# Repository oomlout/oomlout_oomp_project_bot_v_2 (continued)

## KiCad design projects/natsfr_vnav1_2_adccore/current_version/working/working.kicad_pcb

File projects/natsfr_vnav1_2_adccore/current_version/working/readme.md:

# vnav1_2
 
## summary 
* id: natsfr_vnav1_2_adccore
* user: natsfr
* name: vnav1_2
* board: adccore
* repo: https://github.com/natsfr/VNAV1.2
* src_file_repo_kicad_pcb: board/VNAV1/adccore.kicad_pcb
* src_file_repo_kicad_pcb_link: https://github.com/natsfr/VNAV1.2/tree/master/board/VNAV1/adccore.kicad_pcb
* src_file_repo_kicad_sch: board/VNAV1/ad4355.kicad_sch
* src_file_repo_kicad_sch_link: https://github.com/natsfr/VNAV1.2/tree/master/board/VNAV1/ad4355.kicad_sch

* src_file_repo_sch: 
* src_file_repo_sch_link: https://github.com/natsfr/VNAV1.2/tree/master/
* full details link: https://github.com/oomlout/oomlout_oomp_project_bot_v_2/tree/main/projects/natsfr_vnav1_2_adccore/current_version/working

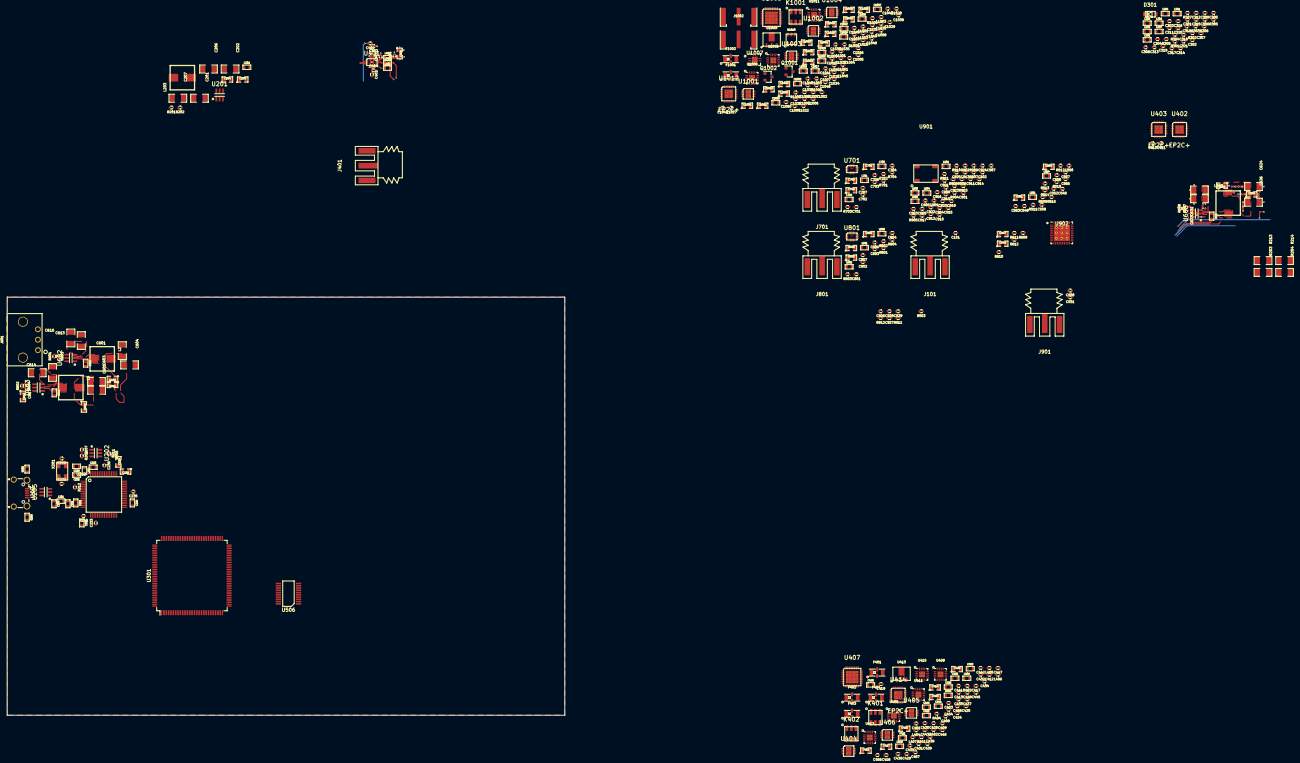
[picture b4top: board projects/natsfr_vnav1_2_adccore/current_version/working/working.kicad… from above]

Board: 4 copper layers, 160.0 x 120.0 mm, 419 parts (1 on the bottom side), 264 nets.

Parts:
C101, C401, C402, C403, C404, C406, C407, C410, C411, C701, C702, C703, C704, C706, C707, C801, C802, C803, C804, C806, C807: CAP_0402; SM0402
C201, C202, C206, C207, C601, C603, C604, C605, C613, C614, C616, C617, C624, C626, C631, C633: 10uF; SM1206
C204, C608, C609, C628: 100nF; SM0805
C205, C611, C612, C630, C1050, C1051, C1053, C1056: 1uF; SM0805
C208, C618, C619, C637: 100nF; SM0603
C221, C223, C224: 100n; SM0603
C222, C226: 10p; SM0402
C225, C229: 4.7u; SM0805
C227: 1uF; SM0603
C228, C230, C231, C232: CAP_0603; SM0603
C233, C234, C235, C236: 100n; SM0402
C301, C302, C304, C305, C307, C308, C310, C311, C313, C314, C316, C317, C319, C320, C548, C549, C550, C552, C555, C901, C902, C904, C906, C907, C908, C909, C911, C912, C914, C916, C919, C920, C923, C926, C927, C928, C929: 10nF; SM0402
C303, C306, C309, C312, C315, C318, C321, C433, C434, C441, C553, C556, C903, C905, C910, C913, C915, C917, C922, C924: 100pF; SM0402
C405, C705, C805: CAP_0805; SM0805
C408, C412, C424, C429, C430, C432, C438, C440, C557, C921, C925, C930, C931, C1001, C1003, C1015, C1021, C1022, C1028, C1032, C1034, C1041: 100nF; SM0402
C409, C413, C417, C425, C431, C437, C439, C443, C558, C1002, C1004, C1005, C1016, C1027, C1031, C1033, C1036, C1037, C1040, C1055, C1059, C1060, C1061: 10pF; SM0402
C414, C415, C416, C426, C427, C428, C1008, C1009, C1010, C1011, C1023, C1024, C1025, C1026: 10uF; SM0805
C418, C1006: 390pF; SM0402
C419, C1007: 33nF; SM0402
C420, C1012: 1500pF; SM0402
C421, C422, C423, C1017, C1018, C1019, C1020: 1nF; SM0603
C435, C436, C442, C454, C456, C457, C458, C1029, C1030, C1035, C1049, C1054: 22pF; SM0402
C444, C446, C448, C450, C452, C455, C1038, C1047, C1052, C1057: 47nF; SM0603
C445, C447, C449, C451, C453, C1039, C1048, C1058: 22p; SM0402
C551, C554: 4.7uF; SM0805
C646, C647, C708, C709, C808, C809: 100uF; SM0805
C918: 15pF; SM0402
C1042, C1043, C1046: 1nF; SM0402
C1044: 5.6pF; SM0402
C1045: 18pF; SM0402
D301: DIODE; SOD-123
F401: LFCN-2500+; FV1206
F402, F1001: LFCN-7200+; FV1206
F403: LFCN-1400+; FV1206
F404, F1002: LFCN-5000+; FV1206
J101, J901: LO Ref output; SMA_AMP_132255-12
J202: USB_OTG; USB_Micro-B_Wuerth_629105150521_CircularHoles
J401, J701, J801: SMA_PCB; SMA_AMP_132255-12
J601: Conn_01x03; MICROFIT_3POS_FEM_43650-0303
J1001: DUT_OUT_1; CINCH_142-0701-881
J1002: DUT_OUT_2; CINCH_142-0701-881
K401, K402, K1001: TCM1-83X-1+; DB1627
L2, L3, L203, L603: 2.2uH; IND_7x7x4.5
L201, L202, L401, L402, L403, L701, L702, L703, L801, L802, L803: IND_0603; SM0603
L301, L302, L303, L304, L305, L306, L307, L501, L514, L901, L902, L903, L904: BLM18; SM0603
L404, L405, L406, L407, L1001, L1002: 7.5nH; SM0402
L408, L1006: 33n; SM0603
L1003: NC; SM0402
L1004, L1005: IND_0805; SM0805
Q1001: BSS84; SOT-23
Q1002: BSS138; SOT-23
R201, R207, R208, R211, R306, R307, R601, R602, R607, R1007, R1008, R1009: 10k; SM0402
R202: 65k; SM0402
R203, R204, R213, R214: RES_1206; SM1206
R205, R206: NP; SM0603
R209: 2.2k; SM0402
R210, R403, R509, R510, R511, R512, R513, R514, R903, R904, R905, R906, R1004: 1k; SM0402
R212: 12k; SM0402
R301, R302, R303, R304, R305, R308, R515, R612, R704, R804: 0; SM0402
R401, R404, R1001, R1002, R1005: 4.7k; SM0402
R402, R901, R902, R1003: RES_0402; SM0402
R405: 49; SM0603
R503, R907, R908, R909, R910: 50; SM0402
R603: 31.6k; SM0402
R604: 4.99k; SM0402
R608: 52.3k; SM0402
R609, R610, R701, R702, R801, R802: 25; SM0402
R611, R703, R803: DNI; SM0402
R911, R912: 100; SM0402
R1006: 38; SM0603
U201, U602, U603, U606: TPS563208_SOT236; SOT-236-095mm
U202: 93LC46B; SOT-236-095mm
U203: FT2232H; LQFP_64
U205: TPD4E1U06-SC70; SOT-236-095mm
U301: ICE40HX1K-TQ144; TQFP-144_20x20mm_P0.5mm
U401, U701, U801: LTC5548; QFN12_2x3mm_UDB_LT
U402, U403, U414, U1012: EP2C+; QFN24_4x4_0.5mm
U404, U1001, U1002: ADM7170ACPZ-5.0; DFN8_3x3mm
U405, U406, U1003, U1004: ADM7170ACPZ-3.3; DFN8_3x3mm
U407: ADF4355; QFN32_5x5mm_3.6mm
U408, U409, U410, U411, U412, U1006, U1008: PE42553; QFN-16_EP_3x3_Pitch0.5mm
U413, U1009: SKY65013-70LF; SOT89-SKY65013-70
U506: ADS131M03_TSSOP; TSSOP20_5.8W
U901: 16.384MHz; IQD_CFPT-126
U902: SI5332A-D-GM2; SI5332A_QFN40_EP_5.9x5.9_Pitch0.5mm
U1005: ADF5355; QFN32_5x5mm_3.6mm
U1007: TSS-183A+; DQ849
U1010: LTC1983; SOT23-6
U1011: PE42520; QFN-16_EP_3x3_Pitch0.5mm
X201: TXC_50X32_AB; XTAL_5.0x3.2mm

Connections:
+1V2: C304.1, C307.1, C603.1, L302.2, L303.2, R203.1, R604.1
+3.3VA: C228.1, C229.2, C230.1, C233.1, C234.1, C235.1, C236.1, C301.1, C310.1, C313.1, C316.1, C319.1, C405.2, C406.2, C551.1, C554.2, C601.1, C705.2, C706.2, C805.2, C806.2, C901.1, C906.1, C907.1, C911.1, C919.1, C1056.2, D301.A, L201.1, L202.1, L301.2, L304.2, L305.2, L306.2, L307.2, L401.2, L501.2, L514.2, L701.2, L801.2, L901.2, L902.2, L903.2, L904.2, Q1001.2 (S), R204.1, R207.2, R208.2, R210.2, R211.2, R306.1, R307.1, R603.1, R611.1, R703.1, R803.1, R905.1, R906.1, U202.6 (VCC), U203.20 (VCCIO), U203.31 (VCCIO), U203.42 (VCCIO), U203.50 (VREGIN), U203.56 (VCCIO), U902.4 (VDD_XTAL)
+5V: C624.1, R213.1, R608.1
+6V: C201.1, C414.1, C415.1, C416.1, C1008.1, C1009.1, C1010.1, C1011.1, R214.1, U404.7 (Vin), U404.8 (Vin), U405.7 (Vin), U405.8 (Vin), U406.7 (Vin), U406.8 (Vin), U1001.7 (Vin), U1001.8 (Vin), U1002.7 (Vin), U1002.8 (Vin), U1003.7 (Vin), U1003.8 (Vin), U1004.7 (Vin), U1004.8 (Vin)
+12V: C206.1, C207.1, C613.1, C614.1, C616.1, C617.1, C631.1, C633.1, J601.1, U201.3 (VIN), U201.5 (EN), U602.3 (VIN), U602.5 (EN), U603.3 (VIN), U603.5 (EN), U606.3 (VIN), U606.5 (EN)
/ADC/A0_N: C809.2, R510.1, R802.1
/ADC/A0_P: C808.2, R509.1, R801.2
/ADC/A1_N: C709.2, R511.1, R702.1
/ADC/A1_P: C708.2, R512.1, R701.2
/ADC/A2_N: C647.2, R514.1, R610.1
/ADC/A2_P: C646.2, R513.1, R609.2
/ADC/DIN: U301.48 (IOB_33), U506.16 (DIN)
/ADC/DOUT: U301.47 (IOB_32), U506.15 (DOUT)
/ADC/SCLK: U301.49 (IOB_35_GBIN5), U506.14 (SCLK)
/ADC/~CS: U301.45 (IOB_31), U506.12 (~CS)
/ADC/~DRDY: U301.44 (IOB_30), U506.13 (~DRDY)
/ADC/~SYNC/RST: U301.43 (IOB_29), U506.11 (~SYNC/RESET)
/ADC_CLK: R515.2, R910.2
/ANALOG_EN: R401.2, R1001.2, R1002.2, U301.22 (IOL_7B), U404.5 (EN), U405.5 (EN), U406.5 (EN), U1001.5 (EN), U1002.5 (EN), U1003.5 (EN), U1004.5 (EN)
/Clocking/FILT_3V3: C902.1, C903.2, C904.1, C905.2, C908.1, C910.2, C912.1, C913.2, C916.1, C917.2, C920.1, C922.2, L901.1, U902.15 (VDDO0), U902.18 (VDDO1), U902.25 (VDDO2), U902.28 (VDDO3), U902.33 (VDDO4), U902.40 (VDDO5)
/Clocking/SCLK: R905.2, U301.34 (IOL_12B), U902.11 (SCLK)
/Clocking/SDATA: R906.2, U301.33 (IOL_12A), U902.12 (SDATA)
/FPGA/D_N: J202.2 (D-), U203.7 (DM), U205.4 (D2-)
/FPGA/D_P: J202.3 (D+), U203.8 (DP), U205.6 (D1-)
/FPGA/F_CLKOUT: U203.32 (ACBUS5), U301.128 (IOT_84_GBIN1)
/FPGA/F_OE: U203.33 (ACBUS6), U301.120 (IOT_81)
/FPGA/F_RD: U203.28 (ACBUS2), U301.129 (IOT_85_GBIN0)
/FPGA/F_RXF: U203.26 (ACBUS0), U301.135 (IOT_88)
/FPGA/F_SIWU: U203.30 (ACBUS4), U301.121 (IOT_82)
/FPGA/F_TXE: U203.27 (ACBUS1), U301.134 (IOT_87)
/FPGA/F_WR: U203.29 (ACBUS3), U301.122 (IOT_83)
/FPGA/ICE40_DONE: R308.1, U203.45 (BDBUS6)
/FPGA/LO_CLK: U301.29 (IOL_10B), U407.1 (CLK)
/FPGA/LO_DATA: U301.28 (IOL_10A), U407.2 (DATA)
/FPGA/LO_LE: U301.31 (IOL_11A), U407.3 (LE)
/FPGA/LO_LOCK: U301.32 (IOL_11B), U407.30 (MUXOUT)
/FPGA/SIGGEN_CLK: U301.24 (IOL_8B), U1005.1 (CLK)
/FPGA/SIGGEN_DATA: U301.23 (IOL_8A), U1005.2 (DATA)
/FPGA/SIGGEN_LE: U301.25 (IOL_9A), U1005.3 (LE)
/FPGA/SIGGEN_LOCK: U301.26 (IOL_9B), U1005.30 (MUXout)
/FPGA/SPI_CLK: R303.2, U203.38 (BDBUS0)
/FPGA/SPI_MISO: R301.2, U203.40 (BDBUS2)
/FPGA/SPI_MOSI: R302.2, U203.39 (BDBUS1)
/FPGA/fd0: U203.16 (ADBUS0), U301.144 (IOT_96)
/FPGA/fd1: U203.17 (ADBUS1), U301.143 (IOT_95)
/FPGA/fd2: U203.18 (ADBUS2), U301.142 (IOT_94)
/FPGA/fd3: U203.19 (ADBUS3), U301.141 (IOT_93)
/FPGA/fd4: U203.21 (ADBUS4), U301.139 (IOT_92)
/FPGA/fd5: U203.22 (ADBUS5), U301.138 (IOT_91)
/FPGA/fd6: U203.23 (ADBUS6), U301.137 (IOT_90)
/FPGA/fd7: U203.24 (ADBUS7), U301.136 (IOT_89)
/FPGA/~ICE40_RST: R305.2, U203.46 (BDBUS7)
/FPGA/~SPI_CS: R304.2, U203.43 (BDBUS4)
/FPGA_CLK: R908.2, U301.50 (IOB_36_GBIN4)
/LO_BANDSEL: U301.11 (IOL_5A), U412.14 (CTRL)
/LO_HB1: U301.8 (IOL_3B), U409.14 (CTRL)
/LO_HB2: U301.10 (IOL_4B), U411.14 (CTRL)
/LO_LB1: U301.7 (IOL_3A), U408.14 (CTRL)
/LO_LB2: U301.9 (IOL_4A), U410.14 (CTRL)
/Mixer DUT1/dut_lo: C701.2, C702.1, U701.11 (LO)
/Mixer DUT1/dut_rf: C703.2, C704.2, U701.5 (RF)
/Mixer DUT1/dut_rf_0: C703.1, J701.1 (sig)
/Mixer DUT1/mx_d_3v3: C707.2, L701.1, U701.9 (Vcc)
/Mixer DUT2/dut_lo: C801.2, C802.1, U801.11 (LO)
/Mixer DUT2/dut_rf: C803.2, C804.2, U801.5 (RF)
/Mixer DUT2/dut_rf_0: C803.1, J801.1 (sig)
/Mixer DUT2/mx_d_3v3: C807.2, L801.1, U801.9 (Vcc)
/Mixer DUT/dut_lo: C401.2, C402.1, U401.11 (LO)
/Mixer DUT/dut_rf: C403.2, C404.2, U401.5 (RF)
/Mixer DUT/dut_rf_0: C403.1, J401.1 (sig)
/Mixer DUT/mx_d_3v3: C407.2, L401.1, U401.9 (Vcc)
/OUTPUT_PA_ON: Q1001.1 (G), R1007.1, U301.21 (IOL_7A_GBIN6)
/PLL DUT/-5V: C1051.1, Q1002.2 (S), R1008.2, U1010.2 (Vout)
/PLL DUT/D1_0: C1060.2, J1001.1 (sig)
/PLL DUT/D1_1: C1060.1, U1012.19 (RF1)
/PLL DUT/D2_0: C1061.2, J1002.1 (sig)
/PLL DUT/D2_1: C1061.1, U1012.12 (RF2)
/PLL DUT/D_0: C1059.2, U1012.3 (RFS)
/PLL DUT/D_1: C1059.1, U1011.7 (RFC)
/PLL DUT/D_HB_0: C1055.2, U1011.11 (RF2)
/PLL DUT/D_HB_1: C1055.1, U1007.5 (RFOUT)
/PLL DUT/D_HB_2: C1040.2, U1007.2 (RFIN)
/PLL DUT/D_HB_3: C1037.2, C1040.1, L1003.1
/PLL DUT/D_HB_4: C1037.1, U1005.14 (RFoutB)
/PLL DUT/D_LB_0: C1054.2, U1011.2 (RF1)
/PLL DUT/D_LB_1: C1054.1, L1006.2, U1009.3 (OUT)
/PLL DUT/D_LB_2: C1049.2, U1009.1 (IN)
/PLL DUT/D_LB_3: C1049.1, U1008.7 (RFC)
/PLL DUT/D_LB_4: C1035.2, U1006.7 (RFC)
/PLL DUT/D_LB_5: C1035.1, K1001.3 (PDOT)
/PLL DUT/D_LB_H_0: F1001.3 (RFOUT), U1008.11 (RF2)
/PLL DUT/D_LB_H_1: F1001.1 (RFIN), U1006.2 (RF1)
/PLL DUT/D_LB_L_0: F1002.3 (RFOUT), U1008.2 (RF1)
/PLL DUT/D_LB_L_1: F1002.1 (RFIN), U1006.11 (RF2)
/PLL DUT/VG_AMP: C1043.1, L1005.2, Q1002.3 (D), R1009.2, U1007.4 (VG2)
/PLL DUT/Vamp: C1050.1, U1010.1 (Vcc), U1010.6 (~SHDN)
/PLL DUT/Vtune: C1006.1, R1003.1, U1005.20 (VTune)
/PLL DUT/Vvco: C1005.1, C1024.1, C1028.1, C1031.1, U1002.1 (Vout), U1002.2 (Vout), U1002.3 (Sense), U1005.6 (Vp), U1005.17 (Vvco), U1005.19 (Vregvco)
/PLL DUT/p_a_0_N: C1029.1, L1002.2, U1005.12 (RFoutA-)
/PLL DUT/p_a_0_P: C1030.2, L1001.2, U1005.11 (RFoutA+)
/PLL DUT/p_a_1_N: C1029.2, K1001.5 (SDOT)
/PLL DUT/p_a_1_P: C1030.1, K1001.4 (S)
/PLL DUT/pll_3v3: C1001.1, C1002.1, C1003.1, C1004.1, C1022.1, C1025.1, C1027.1, U1003.1 (Vout), U1003.2 (Vout), U1003.3 (Sense), U1005.4 (CE), U1005.5 (Avdd), U1005.16 (Avdd), U1005.26 (PDBrf), U1005.27 (Dvdd)
/PLL DUT/pll_vrf: C1016.1, C1026.1, L1001.1, L1002.1, U1004.1 (Vout), U1004.2 (Vout), U1004.3 (Sense), U1005.10 (Vrf)
/PLL/LO_0: C401.1, C456.2, U403.19 (RF1), U414.3 (RFS)
/PLL/LO_1: C456.1, C701.1, L408.2, U403.12 (RF2), U413.3 (OUT)
/PLL/LO_1_1: C458.1, U414.12 (RF2)
/PLL/LO_2: C101.1, C454.2, U402.19 (RF1), U413.1 (IN)
/PLL/LO_2_1: C457.1, U414.19 (RF1)
/PLL/LO_3: C454.1, C801.1, U402.12 (RF2), U412.7 (RFC)
/PLL/LO_HH_0: F402.3 (RFOUT), U411.11 (RF2)
/PLL/LO_HH_1: F402.1 (RFIN), U409.2 (RF1)
/PLL/LO_HL_0: F404.3 (RFOUT), U411.2 (RF1)
/PLL/LO_HL_1: F404.1 (RFIN), U409.11 (RF2)
/PLL/LO_H_0: U411.7 (RFC), U412.11 (RF2)
/PLL/LO_H_1: C442.2, U409.7 (RFC)
/PLL/LO_H_2: C442.1, K402.3 (PDOT)
/PLL/LO_LH_0: F401.3 (RFOUT), U410.11 (RF2)
/PLL/LO_LH_1: F401.1 (RFIN), U408.2 (RF1)
/PLL/LO_LL_0: F403.3 (RFOUT), U410.2 (RF1)
/PLL/LO_LL_1: F403.1 (RFIN), U408.11 (RF2)
/PLL/LO_L_0: U410.7 (RFC), U412.2 (RF1)
/PLL/LO_L_1: C441.2, U408.7 (RFC)
/PLL/LO_L_2: C441.1, K401.3 (PDOT)
/PLL/Vtune: C418.1, R402.1, U407.20 (Vtune)
/PLL/Vvco: C417.1, C426.1, C432.1, C437.1, U404.1 (Vout), U404.2 (Vout), U404.3 (Sense), U407.6 (Vp), U407.17 (Vvco), U407.19 (Vregvco)
/PLL/XO_N: C927.2, U407.28 (REFinB)
/PLL/XO_P: C926.2, U407.29 (REFinA)
/PLL/p_a_0_N: C435.1, L407.2, U407.15 (RfoutB-)
/PLL/p_a_0_P: C436.2, L405.2, U407.14 (RfoutB+)
/PLL/p_a_1_N: C435.2, K402.5 (SDOT)
/PLL/p_a_1_P: C436.1, K402.4 (S)
/PLL/p_b_0_N: C433.1, L406.2, U407.12 (RfoutA-)
/PLL/p_b_0_P: C434.2, L404.2, U407.11 (RfoutA+)
/PLL/p_b_1_N: C433.2, K401.5 (SDOT)
/PLL/p_b_1_P: C434.1, K401.4 (S)
/PLL/pll_3v3: C408.1, C409.1, C412.1, C413.1, C427.1, C430.1, C431.1, U405.1 (Vout), U405.2 (Vout), U405.3 (Sense), U407.4 (CE), U407.5 (Avdd), U407.16 (Avdd), U407.26 (PDBrf), U407.27 (Dvdd)
/PLL/pll_vrf: C425.1, C428.1, L404.1, L405.1, L406.1, L407.1, U406.1 (Vout), U406.2 (Vout), U406.3 (Sense), U407.10 (Vrf)
/PSU/1V2_SW: C619.1, L3.2, U603.2 (SW)
/PSU/3V3_SW: C618.1, L2.2, U602.2 (SW)
/PSU/5V_SW: C637.1, L603.2, U606.2 (SW)
/PSU/6V_SW: C208.1, L203.2, U201.2 (SW)
/SIGGEN_BANDSEL: U301.20 (IOL_6B_GBIN7), U1011.14 (CTRL)
/SIGGEN_CLK_N: C929.2, U1005.28 (REFinB)
/SIGGEN_CLK_P: C928.2, U1005.29 (REFinA)
/SIGGEN_LB1: U301.19 (IOL_6A), U1006.14 (CTRL)
/SIGGEN_LB2: U301.12 (IOL_5B), U1008.14 (CTRL)
GND: C201.2, C202.2, C204.2, C205.2, C206.2, C207.2, C221.2, C222.2, C223.2, C224.2, C225.1, C226.2, C227.2, C228.2, C229.1, C230.2, C231.2, C232.2, C233.2, C234.2, C235.2, C236.2, C301.2, C302.2, C303.1, C304.2, C305.2, C306.1, C307.2, C308.2, C309.1, C310.2, C311.2, C312.1, C313.2, C314.2, C315.1, C316.2, C317.2, C318.1, C319.2, C320.2, C321.1, C402.2, C404.1, C405.1, C406.1, C407.1, C408.2, C409.2, C412.2, C413.2, C414.2, C415.2, C416.2, C417.2, C418.2, C420.2, C421.2, C422.2, C423.2, C424.2, C425.2, C426.2, C427.2, C428.2, C429.1, C430.2, C431.2, C432.2, C437.2, C438.2, C439.2, C440.2, C443.2, C444.1, C445.1, C446.1, C447.1, C448.1, C449.1, C450.1, C451.1, C452.1, C453.1, C455.1, C551.2, C552.2, C553.1, C554.1, C555.2, C556.1, C557.1, C558.1, C601.2, C603.2, C604.2, C605.2, C608.2, C609.2, C611.2, C612.2, C613.2, C614.2, C616.2, C617.2, C624.2, C626.2, C628.2, C630.2, C631.2, C633.2, C702.2, C704.1, C705.1, C706.1, C707.1, C802.2, C804.1, C805.1, C806.1, C807.1, C901.2, C902.2, C903.1, C904.2, C905.1, C906.2, C907.2, C908.2, C909.2, C910.1, C911.2, C912.2, C913.1, C914.2, C915.1, C916.2, C917.1, C918.2, C919.2, C920.2, C922.1, C923.2, C924.1, C931.1, C1001.2, C1002.2, C1003.2, C1004.2, C1005.2, C1006.2, C1008.2, C1009.2, C1010.2, C1011.2, C1012.2, C1015.2, C1016.2, C1017.2, C1018.2, C1019.2, C1020.2, C1021.1, C1022.2, C1023.2, C1024.2, C1025.2, C1026.2, C1027.2, C1028.2, C1031.2, C1032.2, C1033.2, C1034.2, C1036.2, C1038.1, C1039.1, C1041.2, C1042.2, C1043.2, C1044.2, C1045.2, C1046.2, C1047.1, C1048.1, C1050.2, C1051.2, C1052.1, C1056.1, C1057.1, C1058.1, F401.2 (GND), F401.4 (GND), F402.2 (GND), F402.4 (GND), F403.2 (GND), F403.4 (GND), F404.2 (GND), F404.4 (GND), F1001.2 (GND), F1001.4 (GND), F1002.2 (GND), F1002.4 (GND), J101.2, J202.5 (GND), J401.2, J601.2, J601.3, J701.2, J801.2, J901.2, J1001.2, J1002.2, K401.2 (PGND), K402.2 (PGND), K1001.2 (PGND), L1003.2, R201.2, R205.2, R206.2, R212.2, R401.1, R403.2, R404.1, R503.1, R601.2, R602.2, R607.2, R612.1, R704.1, R804.1, R902.2, R904.2, R907.2, R909.2, R1001.1, R1002.1, R1004.2, R1005.1, R1007.2, R1009.1, U201.1 (GND), U202.2 (GND), U203.1 (GND), U203.5 (GND), U203.10 (AGND), U203.11 (GND), U203.13 (TEST), U203.15 (GND), U203.25 (GND), U203.35 (GND), U203.47 (GND), U203.51 (GND), U205.2 (GND), U301.5 (GND), U301.13 (GND), U301.14 (GND), U301.35 (GNDPLL), U301.59 (GND), U301.69 (GND), U301.86 (GND), U301.103 (GND), U301.132 (GND), U301.140 (GND), U401.1 (GND), U401.4 (GND), U401.6 (GND), U401.10 (GND), U401.12 (GND), U401.13 (PAD), U402.1 (GND), U402.2 (GND), U402.4 (GND), U402.5 (GND), U402.6 (GND), U402.7 (GND), U402.8 (GND), U402.9 (GND), U402.10 (GND), U402.11 (GND), U402.13 (GND), U402.14 (GND), U402.15 (GND), U402.16 (GND), U402.17 (GND), U402.18 (GND), U402.20 (GND), U402.21 (GND), U402.22 (GND), U402.23 (GND), U402.24 (GND), U402.25 (PAD), U403.1 (GND), U403.2 (GND), U403.4 (GND), U403.5 (GND), U403.6 (GND), U403.7 (GND), U403.8 (GND), U403.9 (GND), U403.10 (GND), U403.11 (GND), U403.13 (GND), U403.14 (GND), U403.15 (GND), U403.16 (GND), U403.17 (GND), U403.18 (GND), U403.20 (GND), U403.21 (GND), U403.22 (GND), U403.23 (GND), U403.24 (GND), U403.25 (PAD), U404.6 (GND), U404.9 (PAD), U405.6 (GND), U405.9 (PAD), U406.6 (GND), U406.9 (PAD), U407.8 (Cpgnd), U407.9 (Agnd), U407.13 (Agndrf), U407.18 (Agndvco), U407.21 (Agndvco), U407.31 (Sdgnd), U407.33 (PAD), U408.1 (GND), U408.3 (GND), U408.4 (GND), U408.5 (GND), U408.6 (GND), U408.8 (GND), U408.9 (GND), U408.10 (GND), U408.12 (GND), U408.13 (Vss_ext), U408.15 (LS), U408.17 (GND), U409.1 (GND), U409.3 (GND), U409.4 (GND), U409.5 (GND), U409.6 (GND), U409.8 (GND), U409.9 (GND), U409.10 (GND), U409.12 (GND), U409.13 (Vss_ext), U409.15 (LS), U409.17 (GND), U410.1 (GND), U410.3 (GND), U410.4 (GND), U410.5 (GND), U410.6 (GND), U410.8 (GND), U410.9 (GND), U410.10 (GND), U410.12 (GND), U410.13 (Vss_ext), U410.15 (LS), U410.17 (GND), U411.1 (GND), U411.3 (GND), U411.4 (GND), U411.5 (GND), U411.6 (GND), U411.8 (GND), U411.9 (GND), U411.10 (GND), U411.12 (GND), U411.13 (Vss_ext), U411.15 (LS), U411.17 (GND), U412.1 (GND), U412.3 (GND), U412.4 (GND), U412.5 (GND), U412.6 (GND), U412.8 (GND), U412.9 (GND), U412.10 (GND), U412.12 (GND), U412.13 (Vss_ext), U412.15 (LS), U412.17 (GND), U413.2 (GND), U413.4 (GND), U414.1 (GND), U414.2 (GND), U414.4 (GND), U414.5 (GND), U414.6 (GND), U414.7 (GND), U414.8 (GND), U414.9 (GND), U414.10 (GND), U414.11 (GND), U414.13 (GND), U414.14 (GND), U414.15 (GND), U414.16 (GND), U414.17 (GND), U414.18 (GND), U414.20 (GND), U414.21 (GND), U414.22 (GND), U414.23 (GND), U414.24 (GND), U414.25 (PAD), U506.2 (AGND), U506.19 (DGND), U602.1 (GND), U603.1 (GND), U606.1 (GND), U701.1 (GND), U701.4 (GND), U701.6 (GND), U701.10 (GND), U701.12 (GND), U701.13 (PAD), U801.1 (GND), U801.4 (GND), U801.6 (GND), U801.10 (GND), U801.12 (GND), U801.13 (PAD), U901.2 (GND), U902.41 (GND), U1001.6 (GND), U1001.9 (PAD), U1002.6 (GND), U1002.9 (PAD), U1003.6 (GND), U1003.9 (PAD), U1004.6 (GND), U1004.9 (PAD), U1005.8 (CPgnd), U1005.9 (Agnd), U1005.13 (Agndrf), U1005.15 (Agndrf), U1005.18 (Agndvco), U1005.21 (Agndvco), U1005.31 (SDgnd), U1005.33 (PAD), U1006.1 (GND), U1006.3 (GND), U1006.4 (GND), U1006.5 (GND), U1006.6 (GND), U1006.8 (GND), U1006.9 (GND), U1006.10 (GND), U1006.12 (GND), U1006.13 (Vss_ext), U1006.15 (LS), U1006.17 (GND), U1007.1 (NC), U1007.6 (NC), U1007.9 (GND), U1008.1 (GND), U1008.3 (GND), U1008.4 (GND), U1008.5 (GND), U1008.6 (GND), U1008.8 (GND), U1008.9 (GND), U1008.10 (GND), U1008.12 (GND), U1008.13 (Vss_ext), U1008.15 (LS), U1008.17 (GND), U1009.2 (GND), U1009.4 (GND), U1010.5 (GND), U1011.1 (GND), U1011.3 (GND), U1011.4 (GND), U1011.5 (GND), U1011.6 (GND), U1011.8 (GND), U1011.9 (GND), U1011.10 (GND), U1011.12 (GND), U1011.13 (Vss), U1011.15 (LS), U1011.17 (PAD), U1012.1 (GND), U1012.2 (GND), U1012.4 (GND), U1012.5 (GND), U1012.6 (GND), U1012.7 (GND), U1012.8 (GND), U1012.9 (GND), U1012.10 (GND), U1012.11 (GND), U1012.13 (GND), U1012.14 (GND), U1012.15 (GND), U1012.16 (GND), U1012.17 (GND), U1012.18 (GND), U1012.20 (GND), U1012.21 (GND), U1012.22 (GND), U1012.23 (GND), U1012.24 (GND), U1012.25 (PAD), X201.2 (GND), X201.4 (GND)
unnamed: C101.2, J101.1 (sig)
unnamed: C202.1, C204.1, C205.1, L203.1, R214.2
unnamed: C208.2, U201.6 (VBST)
unnamed: C221.1, C223.1, C224.1, C225.2, U203.12 (VCORE), U203.37 (VCORE), U203.49 (VREGOUT), U203.64 (VCORE)
unnamed: C222.1, U203.3 (OSCO), X201.1
unnamed: C226.1, U203.2 (OSCI), X201.3
unnamed: C227.1, R210.1, U203.14 (~RESET)
unnamed: C231.1, L201.2, U203.9 (VPLL)
unnamed: C232.1, L202.2, U203.4 (VPHY)
unnamed: C302.1, C303.2, L301.1, U301.72 (VCC_SPI)
unnamed: C305.1, C306.2, L302.1, U301.27 (VCC), U301.51 (VCC), U301.92 (VCC), U301.111 (VCC)
unnamed: C308.1, C309.2, L303.1, U301.36 (VCCPLL)
unnamed: C311.1, C312.2, L304.1, U301.123 (VCCIO_0), U301.133 (VCCIO_0)
unnamed: C314.1, C315.2, L305.1, U301.6 (VCCIO_3), U301.30 (VCCIO_3)
unnamed: C317.1, C318.2, L306.1, U301.89 (VCCIO_1), U301.100 (VCCIO_1)
unnamed: C320.1, C321.2, L307.1, U301.46 (VCCIO_2), U301.57 (VCCIO_2)
unnamed: C410.1, C458.2
unnamed: C410.2, U402.3 (RFS)
unnamed: C411.1, C457.2
unnamed: C411.2, U403.3 (RFS)
unnamed: C419.1, C420.1, R402.2, U407.7 (Cpout)
unnamed: C419.2, R403.1
unnamed: C421.1, U404.4 (SS)
unnamed: C422.1, U405.4 (SS)
unnamed: C423.1, U406.4 (SS)
unnamed: C424.1, U407.32 (Creg2)
unnamed: C429.2, U407.25 (Creg1)
unnamed: C438.1, C439.1, U407.23 (Vref)
unnamed: C440.1, C443.1, U407.24 (Vbias)
unnamed: C548.1, R510.2, U506.4 (A0_N)
unnamed: C548.2, R509.2, U506.3 (A0_P)
unnamed: C549.1, R512.2, U506.6 (A1_P)
unnamed: C549.2, R511.2, U506.5 (A1_N)
unnamed: C550.1, R514.2, U506.8 (A2_N)
unnamed: C550.2, R513.2, U506.7 (A2_P)
unnamed: C552.1, C553.2, L501.1, U506.1 (AVDD)
unnamed: C555.1, C556.2, L514.1, U506.20 (DVDD)
unnamed: C557.2, U506.18 (CAP)
unnamed: C558.2, R503.2, R515.1, U506.17 (CLKIN)
unnamed: C604.1, C608.1, C611.1, L2.1, R204.2
unnamed: C605.1, C609.1, C612.1, L3.1, R203.2
unnamed: C618.2, U602.6 (VBST)
unnamed: C619.2, U603.6 (VBST)
unnamed: C626.1, C628.1, C630.1, L603.1, R213.2
unnamed: C637.2, U606.6 (VBST)
unnamed: C646.1, U401.2 (IF_P)
unnamed: C647.1, U401.3 (IF_N)
unnamed: C708.1, U701.2 (IF_P)
unnamed: C709.1, U701.3 (IF_N)
unnamed: C808.1, U801.2 (IF_P)
unnamed: C809.1, U801.3 (IF_N)
unnamed: C909.1, L902.1, R901.2, U901.4 (Vcc)
unnamed: C914.1, C915.2, L903.1, U902.1 (VDD_DIG)
unnamed: C918.1, C921.1, U901.3 (OUT)
unnamed: C921.2, R903.2
unnamed: C923.1, C924.2, L904.1, U902.9 (VDDA)
unnamed: C925.1, R903.1, R904.1
unnamed: C925.2, U902.5 (XA_CLKIN1)
unnamed: C926.1, R911.1, U902.30 (OUT5)
unnamed: C927.1, R911.2, U902.29 (OUT5b)
unnamed: C928.1, R912.1, U902.22 (OUT2)
unnamed: C929.1, R912.2, U902.21 (OUT2b)
unnamed: C930.1, J901.1 (sig)
unnamed: C1007.1, C1012.1, R1003.2, U1005.7 (CPout)
unnamed: C1007.2, R1004.1
unnamed: C1015.1, U1005.32 (Creg2)
unnamed: C1017.1, U1001.4 (SS)
unnamed: C1018.1, U1002.4 (SS)
unnamed: C1019.1, U1003.4 (SS)
unnamed: C1020.1, U1004.4 (SS)
unnamed: C1021.2, U1005.25 (Creg1)
unnamed: C1032.1, C1033.1, U1005.23 (Vref)
unnamed: C1034.1, C1036.1, U1005.24 (Vbias)
unnamed: C1041.1, L1004.1, U1007.8 (VDD1)
unnamed: C1042.1, L1005.1, U1007.3 (VG1)
unnamed: C1053.1, U1010.3 (C+)
unnamed: C1053.2, U1010.4 (C-)
unnamed: D301.K, U301.108 (VPP_2V5)
unnamed: J202.6 (Shield), R205.1, R206.1
unnamed: R307.2, R308.2, U301.65 (CDONE)
unnamed: R305.1, R306.2, U301.66 (~CRESET_B)
unnamed: R304.1, U301.71 (IOB_47_SS)
unnamed: R303.1, U301.70 (IOB_46_SCK)
unnamed: R302.1, U301.68 (IOB_45_SDI)
unnamed: R301.1, U301.67 (IOB_44_SDO)
unnamed: L402.1, U401.7 (EN)
unnamed: L403.1, U401.8 (X2)
unnamed: L408.1, R405.2
unnamed: L702.1, U701.7 (EN)
unnamed: L703.1, U701.8 (X2)
unnamed: L802.1, U801.7 (EN)
unnamed: L803.1, U801.8 (X2)
unnamed: L1006.1, R1006.2
unnamed: Q1001.3 (D), Q1002.1 (G), R1008.1
unnamed: R201.1, R202.2, U201.4 (VFB)
unnamed: R207.1, R209.2, U202.1 (DOUT)
unnamed: R208.1, U202.4 (SCK), U203.62 (EECLK)
unnamed: R209.1, U202.3 (DIN), U203.61 (EEDATA)
unnamed: R211.1, U202.5 (CS), U203.63 (EECS)
unnamed: R212.1, U203.6 (REF)
unnamed: R404.2, U407.22 (Rset)
unnamed: R601.1, R603.2, U602.4 (VFB)
unnamed: R602.1, R604.2, U603.4 (VFB)
unnamed: R607.1, R608.2, U606.4 (VFB)
unnamed: R609.1, R610.2, R611.2, R612.2
unnamed: R701.1, R702.2, R703.2, R704.2
unnamed: R801.1, R802.2, R803.2, R804.2
unnamed: R901.1, R902.1, U901.1 (Vcon)
unnamed: R907.1, U902.13 (OUT0b)
unnamed: R908.1, U902.14 (OUT0)
unnamed: R909.1, U902.16 (OUT1b)
unnamed: R910.1, U902.17 (OUT1)
unnamed: R1005.2, U1005.22 (Rset)
unnamed: C930.2, U902.7 (CLKIN_3)
unnamed: C931.2, U902.8 (CLKIN_3b)
VAMP: C444.2, C445.2, C446.2, C447.2, C448.2, C449.2, C450.2, C451.2, C452.2, C453.2, C455.2, C1023.1, C1038.2, C1039.2, C1044.1, C1045.1, C1046.1, C1047.2, C1048.2, C1052.2, C1057.2, C1058.2, L1004.2, R405.1, R1006.1, U408.16 (Vdd), U409.16 (Vdd), U410.16 (Vdd), U411.16 (Vdd), U412.16 (Vdd), U1001.1 (Vout), U1001.2 (Vout), U1001.3 (Sense), U1006.16 (Vdd), U1007.7 (VDD2), U1008.16 (Vdd), U1011.16 (Vdd)

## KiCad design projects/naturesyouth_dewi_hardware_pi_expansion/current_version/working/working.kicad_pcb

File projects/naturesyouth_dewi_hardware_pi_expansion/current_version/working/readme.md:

# dewi_hardware
 
## summary 
* id: naturesyouth_dewi_hardware_pi_expansion
* user: naturesyouth
* name: dewi_hardware
* board: pi_expansion
* repo: https://github.com/naturesyouth/dewi-hardware
* src_file_repo_kicad_pcb: Pi-Expansion/Pi-Expansion.kicad_pcb
* src_file_repo_kicad_pcb_link: https://github.com/naturesyouth/dewi-hardware/tree/master/Pi-Expansion/Pi-Expansion.kicad_pcb

* src_file_repo_sch: Pi-Expansion/Pi-Expansion.sch
* src_file_repo_sch_link: https://github.com/naturesyouth/dewi-hardware/tree/master/Pi-Expansion/Pi-Expansion.sch
* full details link: https://github.com/oomlout/oomlout_oomp_project_bot_v_2/tree/main/projects/naturesyouth_dewi_hardware_pi_expansion/current_version/working

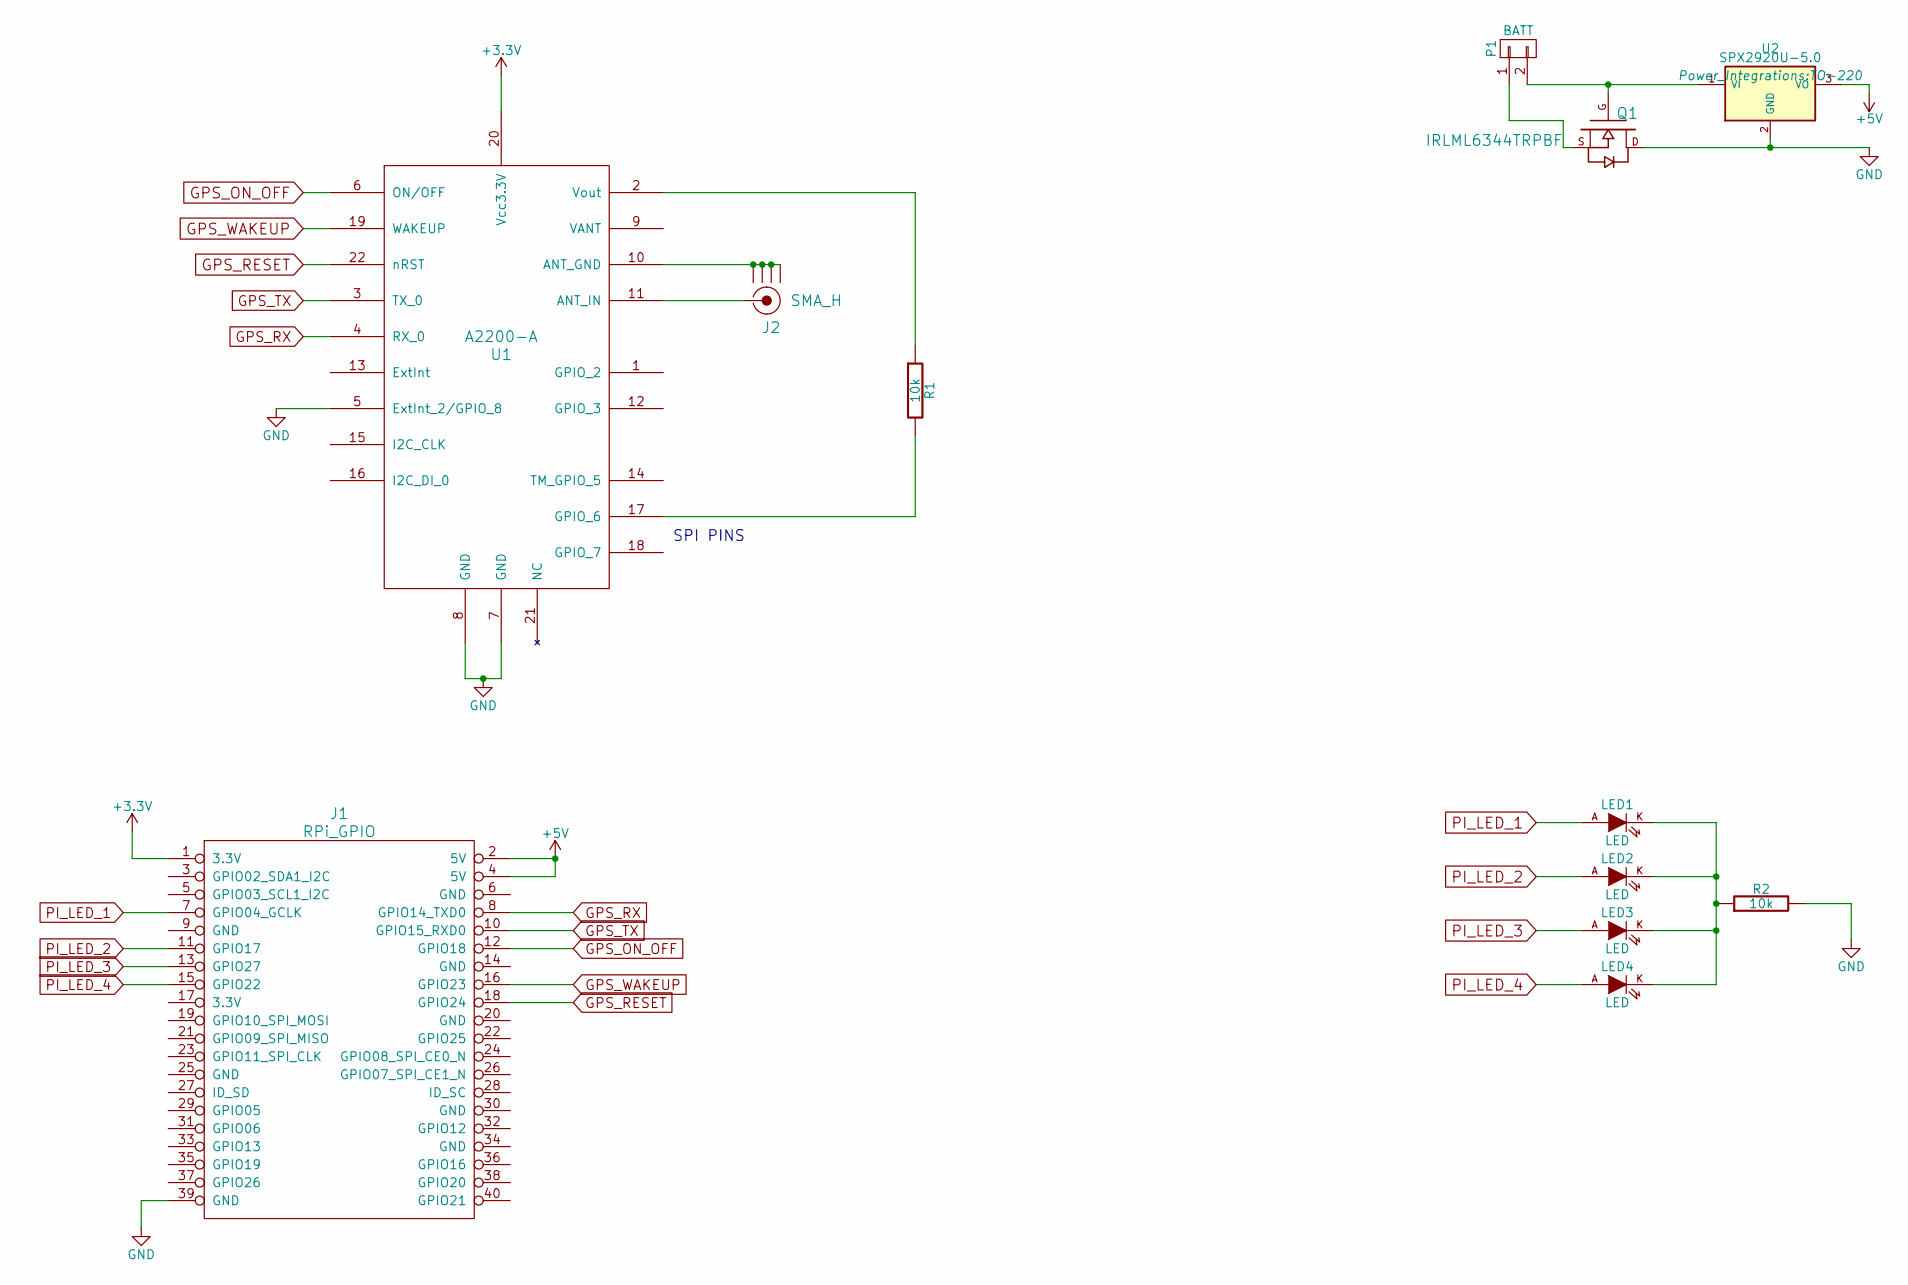
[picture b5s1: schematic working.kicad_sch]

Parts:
J1: RPi_GPIO; Pin_Header_Straight_2x20
J2: SMA_H; Manufacturer Part Number 142-0711-821
LED1, LED2, LED3, LED4: LED; LED-1206
P1: BATT; Socket_MOLEX-KK-RM2-54mm_Lock_2pin_straight
Q1: IRLML6344TRPBF; SOT23_FET
R1, R2: 10k; 1206
U1: A2200-A
U2: SPX2920U-5.0; TO-220

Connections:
+3V3: J1.1 (3.3V), U1.20 (Vcc3.3V)
+5V: J1.2 (5V), J1.4 (5V), U2.3 (VO)
GND: J1.39 (GND), Q1.D, R2.2, U1.5 (ExtInt_2/GPIO_8), U1.7 (GND), U1.8 (GND), U2.2 (GND)
GPS_ON_OFF: J1.12 (GPIO18), U1.6 (ON/OFF)
GPS_RESET: J1.18 (GPIO24), U1.22 (nRST)
GPS_RX: J1.8 (GPIO14_TXD0), U1.4 (RX_0)
GPS_TX: J1.10 (GPIO15_RXD0), U1.3 (TX_0)
GPS_WAKEUP: J1.16 (GPIO23), U1.19 (WAKEUP)
unnamed: J2.1 (RF), U1.11 (ANT_IN)
unnamed: J2.2 (GND1), J2.3 (GND2), J2.4 (GND3), J2.5 (GND4), U1.10 (ANT_GND)
unnamed 37: LED1.K, LED2.K, LED3.K, LED4.K, R2.1; also elsewhere on the board
unnamed: P1.1, Q1.S
unnamed: P1.2, Q1.G, U2.1 (VI)
unnamed: R1.1, U1.2 (Vout)
unnamed: R1.2, U1.17 (GPIO_6)
PI_LED_1: J1.7 (GPIO04_GCLK), LED1.A
PI_LED_2: J1.11 (GPIO17), LED2.A; also elsewhere on the board
PI_LED_3: J1.13 (GPIO27), LED3.A
PI_LED_4: J1.15 (GPIO22), LED4.A

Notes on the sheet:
SPI PINS

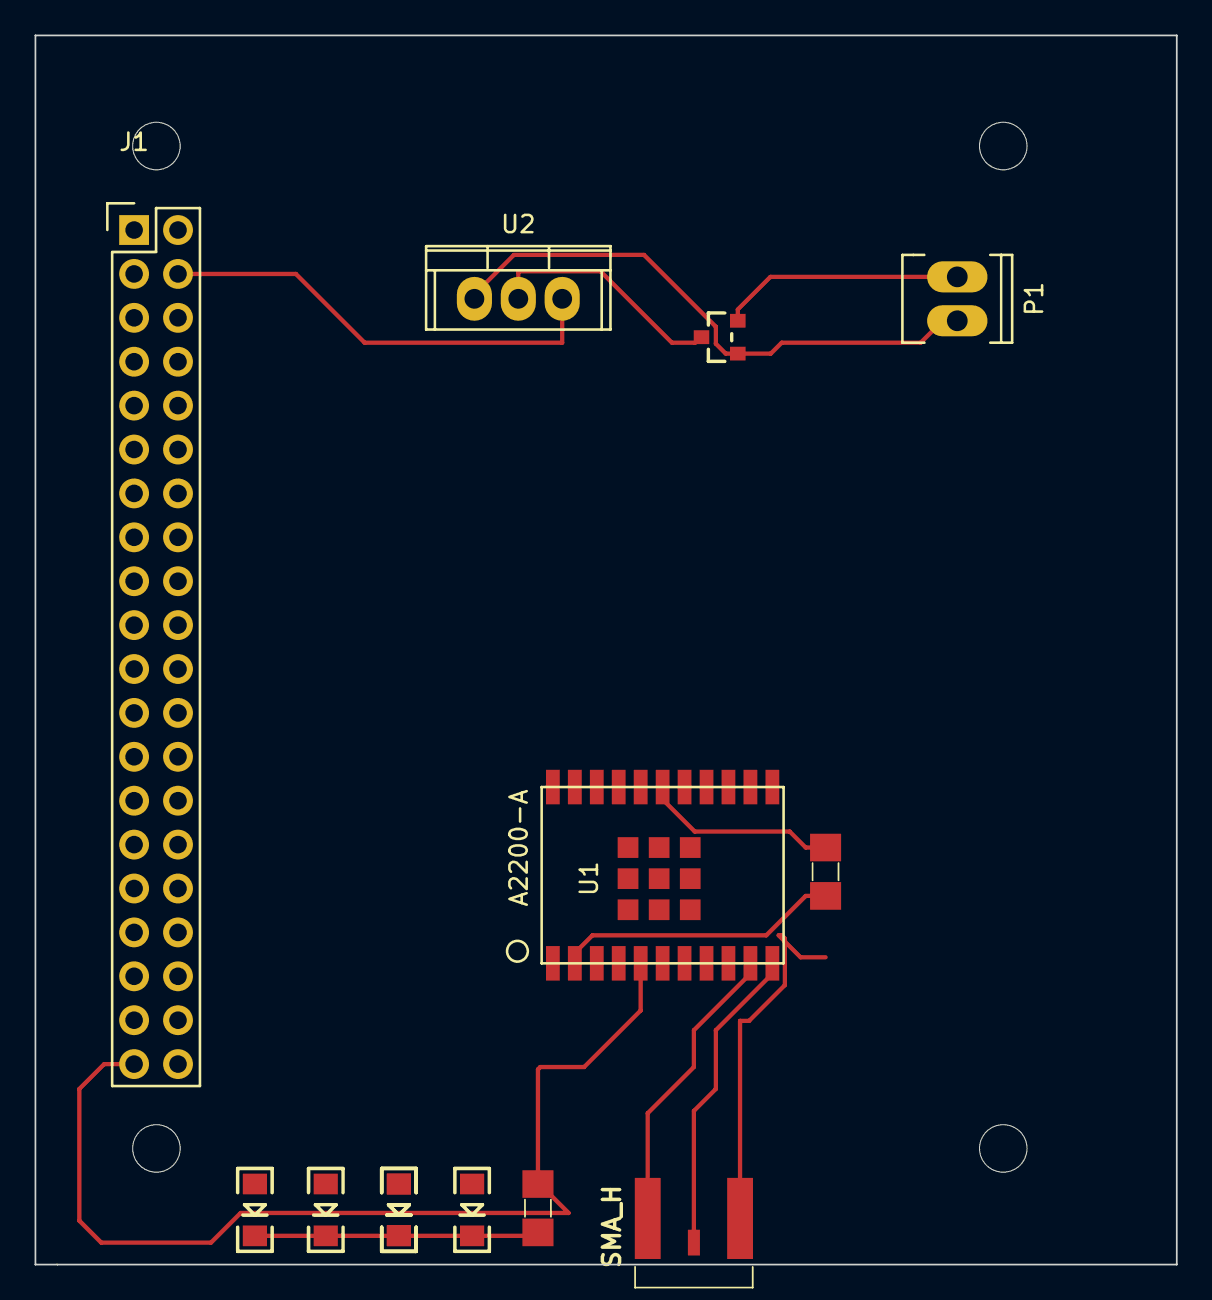
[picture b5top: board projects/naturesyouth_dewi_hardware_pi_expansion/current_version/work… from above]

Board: 2 copper layers, 66.0 x 71.1 mm, 17 parts (0 on the bottom side), 19 nets.

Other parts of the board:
1111, 1112, 1121, 1122: RPi_Hat_Mounting_Hole
LED2#2: LED; LED-1206

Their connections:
unnamed 37: LED2#2.K; also elsewhere on the board
PI_LED_2: LED2#2.A; also elsewhere on the board
